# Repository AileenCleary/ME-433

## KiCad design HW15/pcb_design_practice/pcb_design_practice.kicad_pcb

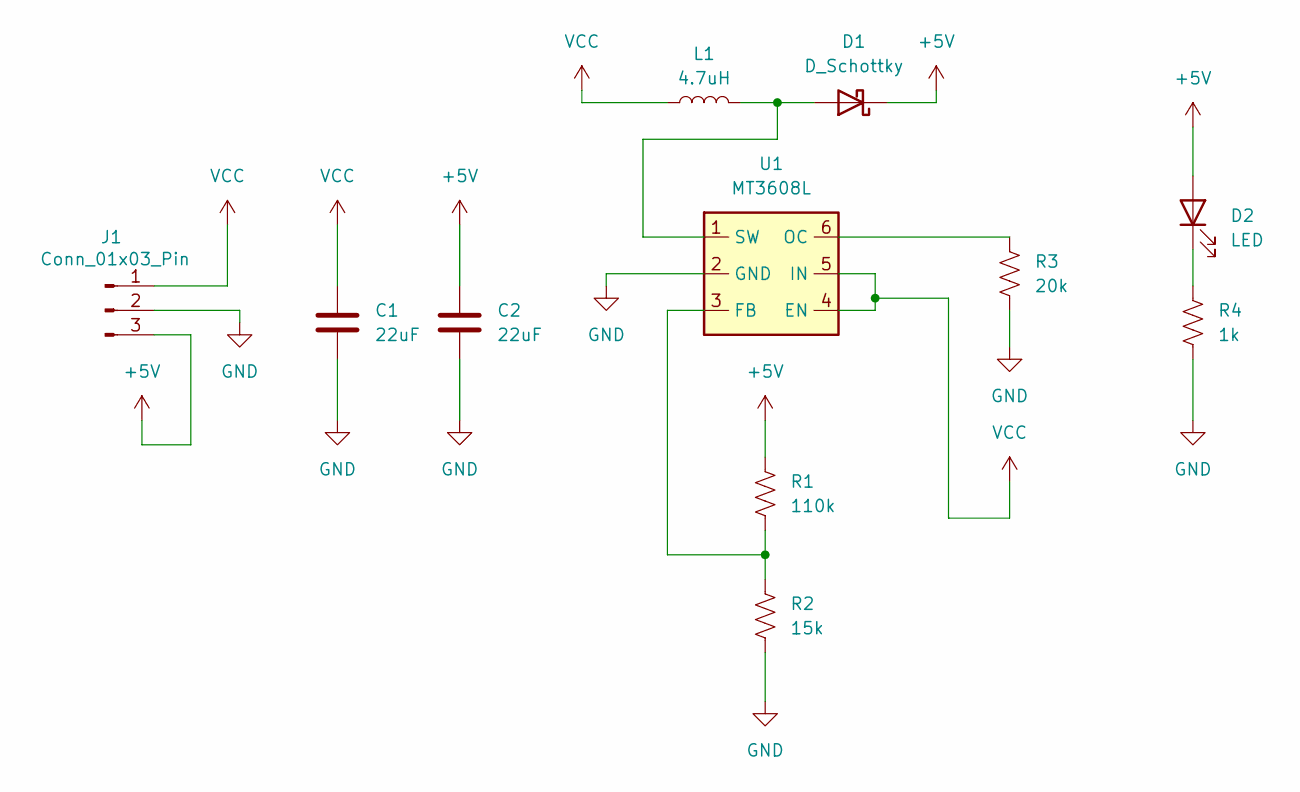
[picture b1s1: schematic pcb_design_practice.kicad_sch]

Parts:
C1, C2: 22uF; CP_Elec_4x3
D1: D_Schottky; D_SOD-123
D2: LED; LED_0805_2012Metric
J1: Conn_01x03_Pin; PinSocket_1x03_P2.54mm_Vertical
L1: 4.7uH; L_0805_2012Metric
R1: 110k; R_0805_2012Metric
R2: 15k; R_0805_2012Metric
R3: 20k; R_0805_2012Metric
R4: 1k; R_0805_2012Metric
U1: MT3608L; SOT-23-6

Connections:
+5V: C2.1, D1.1 (K), D2.2 (A), J1.3, R1.1
GND: C1.2, C2.2, J1.2, R2.2, R3.2, R4.1, U1.2 (GND)
unnamed: D1.2 (A), L1.2, U1.1 (SW)
unnamed: D2.1 (K), R4.2
unnamed: R1.2, R2.1, U1.3 (FB)
unnamed: R3.1, U1.6 (OC)
VCC: C1.1, J1.1, L1.1, U1.4 (EN), U1.5 (IN)

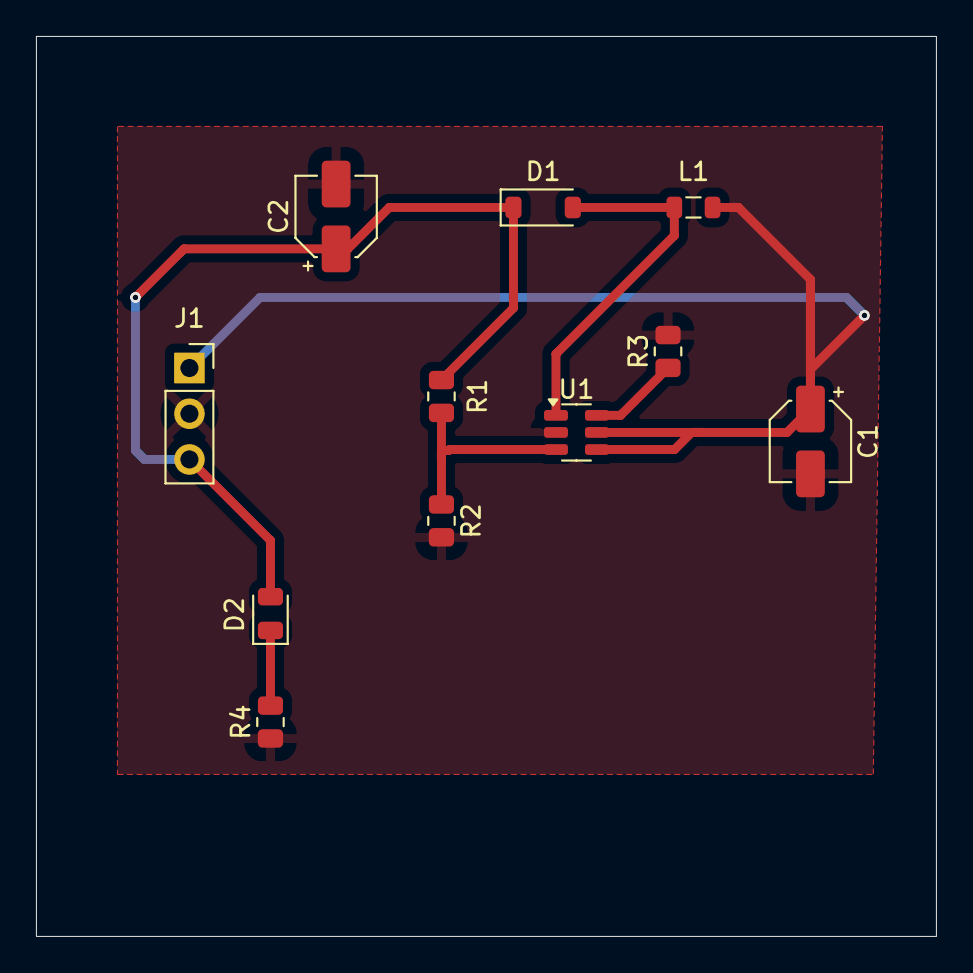
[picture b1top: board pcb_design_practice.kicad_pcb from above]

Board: 2 copper layers, 50.0 x 50.0 mm, 11 parts (0 on the bottom side), 7 nets.

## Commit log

2025-04-03 init
2025-04-06 HW2 done: button counter, toggle LED
2025-04-09 ADC reading
2025-04-09 organize..
2025-04-14 picture of waveform added
2025-04-22 HW6 done
2025-04-23 OLED done
2025-05-07 HW10
2025-05-09 HW 11
2025-05-12 HW12 camera working
2025-05-15 HW IMU
2025-05-24 robot cad assembly vers1 all parts
2025-05-25 pcb board done
2025-05-25 HW16 motor control
2025-06-04 HW12 redo
2025-06-04 HW17
2025-06-05 HW18 tech cup
2025-06-05 background change
2025-06-05 circuit diagram and pics
